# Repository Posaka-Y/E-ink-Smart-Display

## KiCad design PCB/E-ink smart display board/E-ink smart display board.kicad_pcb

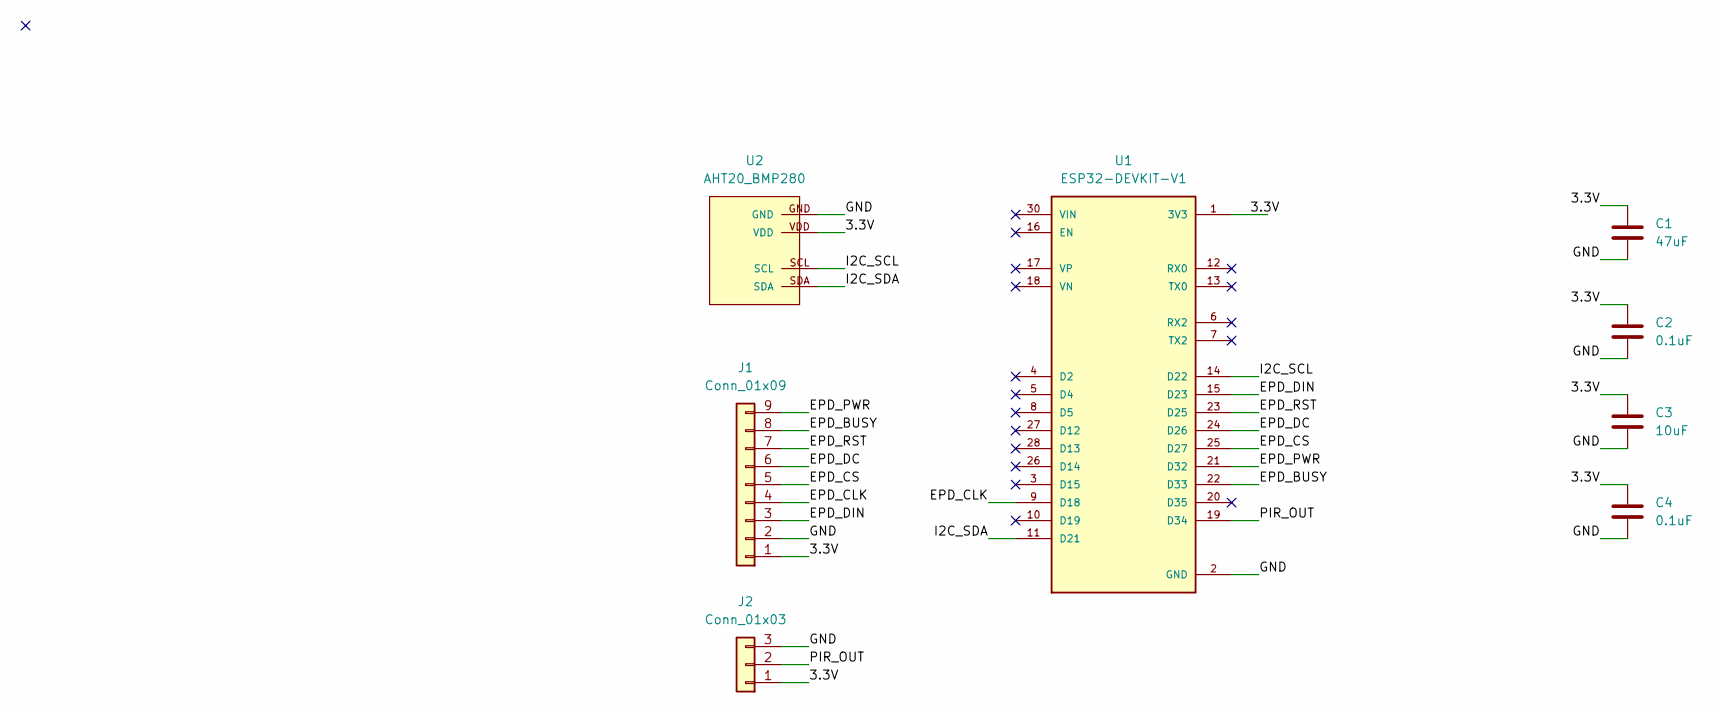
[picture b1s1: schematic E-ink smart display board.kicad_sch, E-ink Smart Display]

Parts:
C1: 47uF; C_0805_2012Metric
C2, C4: 0.1uF; C_0805_2012Metric
C3: 10uF; C_0805_2012Metric
J1: Conn_01x09; PinHeader_1x09_P2.54mm_Vertical
J2: Conn_01x03; JST_XH_B3B-XH-A_1x03_P2.50mm_Vertical
U1: ESP32-DEVKIT-V1; MODULE_ESP32_DEVKIT_V1; PARTREV N/A
U2: AHT20_BMP280

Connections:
/3.3V: C1.1, C2.1, C3.1, C4.1, J1.1, J2.1, U1.1 (3V3), U2.VDD
/EPD_BUSY: J1.8, U1.22 (D33)
/EPD_CLK: J1.4, U1.9 (D18)
/EPD_CS: J1.5, U1.25 (D27)
/EPD_DC: J1.6, U1.24 (D26)
/EPD_DIN: J1.3, U1.15 (D23)
/EPD_PWR: J1.9, U1.21 (D32)
/EPD_RST: J1.7, U1.23 (D25)
/I2C_SCL: U1.14 (D22), U2.SCL
/I2C_SDA: U1.11 (D21), U2.SDA
/PIR_OUT: J2.2, U1.19 (D34)
GND: C1.2, C2.2, C3.2, C4.2, J1.2, J2.3, U1.2 (GND), U1.29 (GND), U2.GND

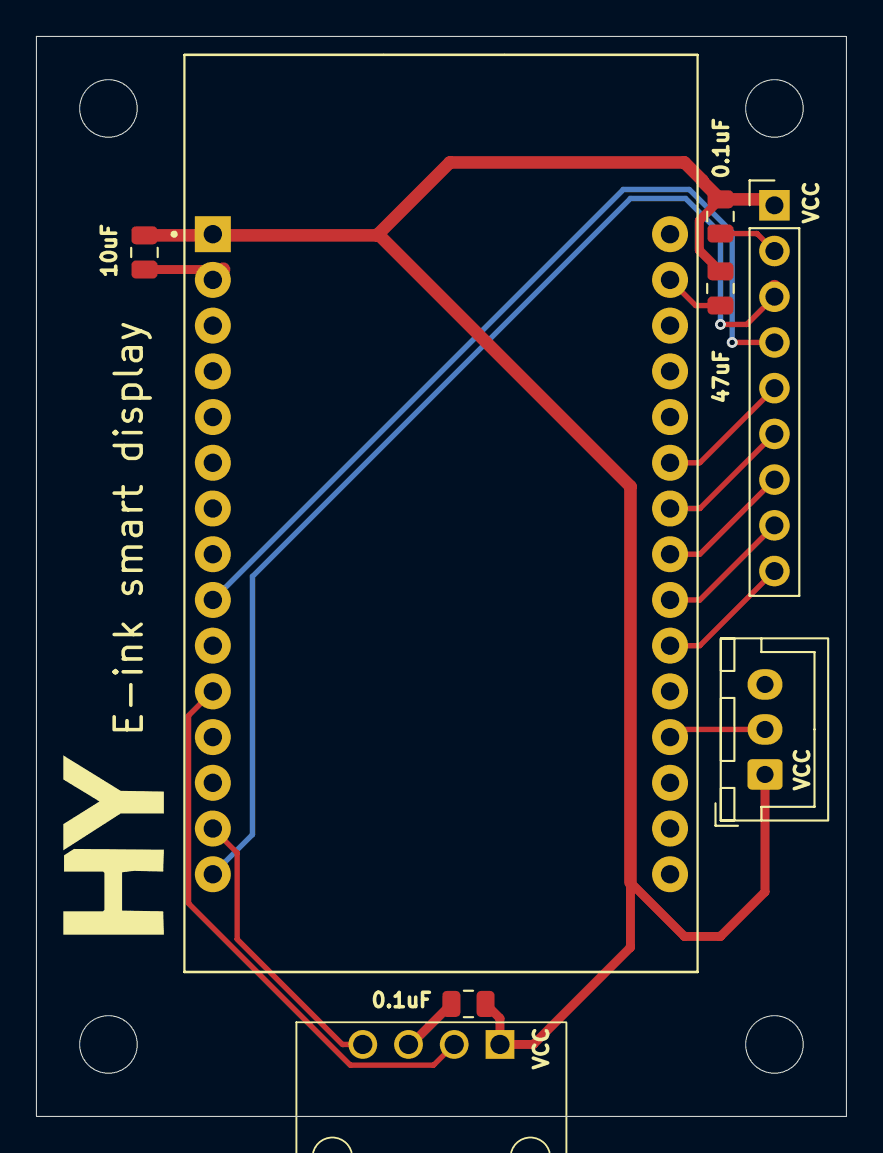
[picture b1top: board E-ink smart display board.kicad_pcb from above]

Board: 2 copper layers, 45.0 x 60.0 mm, 12 parts (0 on the bottom side), 12 nets.

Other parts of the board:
H1, H2, H3, H4: MountingHole_3.2mm_M3

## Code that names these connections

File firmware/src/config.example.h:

#pragma once

// Copy this file to src/config.h and fill in local credentials.
// Keep src/config.h out of Git because it contains Wi-Fi/API secrets.

// Pin assignments
// Default target: ESP32-S3 DevKitC-1
// Alternative targets:
//   - ESP32 DevKit when BOARD_ESP32_DEVKIT is defined
//   - ESP32-C3 SuperMini when BOARD_ESP32C3_SUPERMINI is defined
#if defined(BOARD_ESP32S3_DEVKITC1)
  // ESP32-S3 DevKitC-1
  // Avoid boot strapping pins: GPIO0, GPIO3, GPIO45, GPIO46
  // Avoid native USB pins on many S3 boards: GPIO19, GPIO20
  #define EPD_SCK_PIN     12   // CLK
  #define EPD_MOSI_PIN    11   // DIN
  #define EPD_CS_PIN      10   // CS
  #define EPD_DC_PIN       9   // DC
  #define EPD_RST_PIN     14   // RST
  #define EPD_BUSY_PIN    13   // BUSY
  #define EPD_PWR_PIN     21   // PWR, HIGH=display on, LOW=display off

  #define I2C_SDA_PIN      8   // SDA
  #define I2C_SCL_PIN     18   // SCL

  #define PIR_PIN          4   // PIR OUT
#elif defined(BOARD_ESP32_DEVKIT)
  // ESP32 DevKit / ESP32-WROOM
  // Avoid boot strapping pins: GPIO0, GPIO2, GPIO4, GPIO5, GPIO12, GPIO15
  // Avoid flash pins: GPIO6-GPIO11
  // GPIO34-GPIO39 are input-only; PIR can use GPIO34 if the module drives it.
  #define EPD_SCK_PIN     18   // CLK
  #define EPD_MOSI_PIN    23   // DIN
  #define EPD_CS_PIN      27   // CS
  #define EPD_DC_PIN      26   // DC
  #define EPD_RST_PIN     25   // RST
  #define EPD_BUSY_PIN    33   // BUSY
  #define EPD_PWR_PIN     32   // PWR, HIGH=display on, LOW=display off

  #define I2C_SDA_PIN     21   // SDA
  #define I2C_SCL_PIN     22   // SCL

  #define PIR_PIN         34   // PIR OUT, input-only, ext1 wake capable
#else
  // ESP32-C3 SuperMini
  // E-ink display (software SPI / bit-bang)
  #define EPD_SCK_PIN      6   // CLK
  #define EPD_MOSI_PIN     7   // DIN
  #define EPD_CS_PIN      10   // CS
  #define EPD_DC_PIN       5   // DC
  #define EPD_RST_PIN      3   // RST
  #define EPD_BUSY_PIN     2   // BUSY
  #define EPD_PWR_PIN      8   // PWR, HIGH=display on, LOW=display off

  #define I2C_SDA_PIN     21   // SDA
  #define I2C_SCL_PIN     20   // SCL

  #define PIR_PIN          1   // PIR OUT
#endif

// Wi-Fi
// 0 = WPA2 personal / 1 = WPA2-Enterprise (EAP / PEAP-MSCHAPv2)
#define WIFI_USE_ENTERPRISE  1

#define WIFI_SSID     "your_ssid_here"
#define WIFI_PASSWORD "your_wifi_password_here"  // unused when WIFI_USE_ENTERPRISE=1

// WPA2-Enterprise credentials, used only when WIFI_USE_ENTERPRISE=1
#define EAP_IDENTITY  "anonymous@example.com"
#define EAP_USERNAME  "your_enterprise_username"
#define EAP_PASSWORD  "your_enterprise_password"
#define EAP_DOMAIN    "example.com"

// Optional fixed MAC address.
// Locally administered unicast MACs should have first byte bit0=0 and bit1=1.
#define WIFI_FIXED_MAC  {0x02, 0xAB, 0xCD, 0xEF, 0x12, 0x34}

// Gemini Flash API
#define GEMINI_API_KEY "your_gemini_api_key_here"

// Google Calendar (Apps Script JSON proxy)
// Deploy the Apps Script web app and paste the /exec URL here.
#define GCAL_ENDPOINT "https://script.google.com/macros/s/your_deployment_id/exec"

// NTP
#define NTP_SERVER    "ntp.nict.jp"
#define NTP_OFFSET    32400   // JST = UTC+9 (seconds)
#define NTP_INTERVAL  3600000 // sync every 1 hour (ms)

// Display update interval
#define SLEEP_SECONDS  60

// Sensor I2C
#define BMP280_ADDR  0x77    // SDO->GND=0x76, SDO->VCC=0x77
